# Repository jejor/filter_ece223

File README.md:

# Filter Project for ECE223PSU/MCECS-2019

This repo contains information pertaining to a four branch 6th order passive Butterworth filters, with volume indicators, music box.
This project was completed to meet the 2018-2019 Electrical Engineering 221-223 sequence course requirements taught by Dr. Donald Duncan at Portland State University Maseeh College of Engineering and Computer Science - Electrical Engineering Program. 

View the project final report [here](/docs/finalreport.pdf) or by using the [google doc link](https://docs.google.com/document/d/1vV6OJEWidjzbffv2h6qe4K4YXA2pBC030I1_OhE0v94/edit?usp=sharing)

Note: Github documentation is currently in progress. Refer to the doc/finalreport.pdf until github documentation is completed.

# Filter Project Information

## Project Purpose

The function of this project is to filter an audio signal and indicate, by light, the filtered frequency presence. The audio signal is filtered through four branches, each filter branch has its own adjustable volume/LED indicator which is activated when a signal passes through the filter branch. Below is the block diagram for the circuit design,

## Project Parts

### [Audio/Input Signal](/docs/input_signal.md)

The audio signal (input signal) must fall within human range of hearing (typically 20-20000 Hz). The input into the system is a 3.5mm auxiliary audio connection. The audio is split into a stereo (binaural) and a mono (mixed) branch. The audio system design ensures that the music played over the speakers is kept separate as left and right audio channels and the filtered signal contains all the audio data. The audio data splits are made using NE5532 op amps used as buffers.

Note: The signal input is connected via screw terminal which allows for signal input modularity. Therefore, the 3.5mm auxiliary cable input into the filter branches and following volume indicator circuit can be removed to insert different signal generator.

### [Filter Branches](/docs/filters.md)

There are four 6th order passive Butterworth equal termination filters; one low-pass, two band-passes, and a high pass. These filters are routied and mounted on a custom designed PCB.

Note: 
- Low-Pass: < 200 Hz
- Band-Pass 1: 250 Hz to 4 kHz
- Band-Pass 2: 4.05 kHz to 9.95 kHz
- High-Pass: > 10 kHz

### [Volume Indicators](/docs/volume.md)

At the end of each filter branch is a LED volume indicator circuit. These circuits contain a series of LEDs and an LM3915 (resistor and comparator network). This circuit is used to indicate when an audio signal satisfies the filter frequencies and passes through that branch; the LM3915 is used to indicate the intensity (i.e. volume) of the signal. These circuits will have the display of two rows of 5 green, 3 yellow, and 2 red LEDs, totalling 20 LEDs per branch. There are a total of four volume indicators, each receiving an amplified signal from a filter.  The intensity of each volume indicator is controllable via a potentiometer controlling the gainstage on its respective filter. These circuits were routed and mounted on a custom designed PCB.

### [Power System](/docs/power.md)

Power Requirements:
- Op Amps, +18V and -18V
- LM3915, 12-20V
- LEDs, 3-5V
- Common Ground

To satisfy the power requirements the project uses a total of seven 9V batteries. These seven batteries are split between three battery packs with a common ground. The first battery pack powers all the op amp rails, it is four 9V batteries in series with a voltage divider to define a common ground and supply the +18V and -18V. The second battery pack powers the volume indicator circuit main power and contains two 9V batteries in series to supply +18V. The third battery pack powers the LEDs in the volume indicator circuit by using a single 9V and an LM317 voltage regulator to supply 3.3V.

### [Housing](/housing/README.md)

This project is housed within a pressed wood frame.

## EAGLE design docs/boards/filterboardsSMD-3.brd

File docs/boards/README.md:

# EAGLE Boards

Made using EAGLE 9.3.2

There are two boards and schematic pairs in this folder. 

- lm3915LEDv.1.brd and lm3915LEDv.1.sch were both designed and manufacutured by Jennifer Jordan on May 2nd, 2019.
- filterboardsSMD-3.brd and filterboardsSMD-3.sch were both designed and manufactured by David Lay (dalay@pdx.edu) on May 29th, 2019.

The completed boards can be seen below,

- lm3915LEDv.1 Front

- Back

- filterboardsSMD-3 Front (credit: David Lay)

- Back (credit: David Lay)

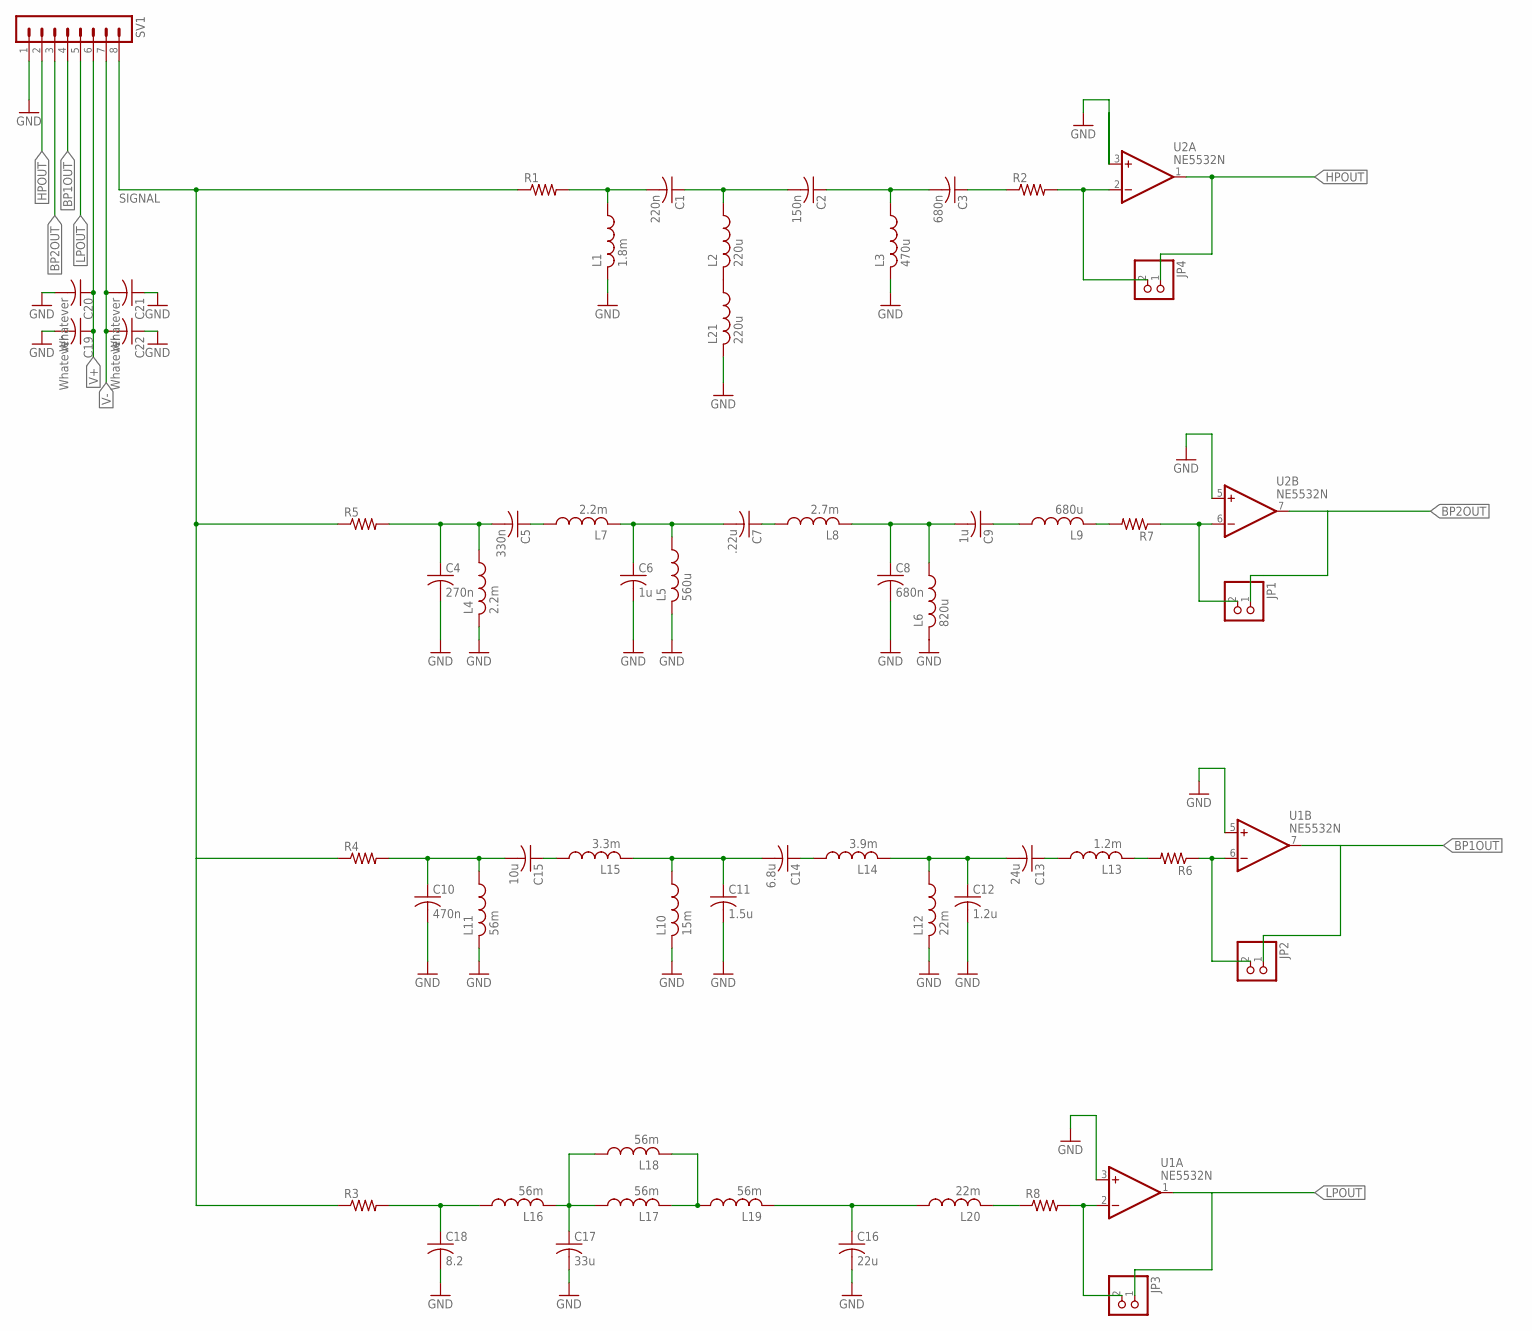
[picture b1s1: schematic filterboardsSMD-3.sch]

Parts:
C1: 220n; C0805K
C2: 150n; C025-030X050
C3, C8: 680n; C025-030X050
C4: 270n; C025-030X050
C5: 330n; C025-030X050
C6, C9: 1u; C1210K
C7: .22u; C0805K
C10: 470n; C025-030X050
C11: 1.5u; C0805K
C12: 1.2u; C102-054X133
C13: 24u; C025-030X050
C14: 6.8u; C025-030X050
C15: 10u; C1206K
C16: 22u; C025-030X050
C17: 33u; C025-030X050
C18: 8.2; C1210K
C19, C20, C21, C22: Whatever; C050-025X075
JP1, JP2, JP3, JP4: PINHD-1X2; 1X02
L1: 1.8m; 0207/5V
L2, L21: 220u; 0207/5V
L3: 470u; 0207/5V
L4, L7: 2.2m; 0207/5V
L5: 560u; 0207/5V
L6: 820u; 0207/5V
L8: 2.7m; 0207/5V
L9: 680u; 0207/5V
L10: 15m; 0207/5V
L11, L16, L17, L18, L19: 56m; 0207/5V
L12, L20: 22m; 0207/5V
L13: 1.2m; 0207/5V
L14: 3.9m; 0207/5V
L15: 3.3m; 0207/5V
R1, R2, R3, R4, R5, R6, R7, R8: R-US_0204/7; 0204/7
SV1: MA08-1
U1, U2: NE5532N; DIL08

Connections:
BP1OUT: JP2.1, SV1.4, U1.7 (OUT)
BP2OUT: JP1.1, SV1.3, U2.7 (OUT)
GND: C4.2, C6.2, C8.2, C10.2, C11.2, C12.2, C16.2, C17.2, C18.2, C19.2, C20.2, C21.1, C22.1, L1.2, L3.2, L4.2, L5.2, L6.2, L10.2, L11.2, L12.2, L21.2, SV1.1, U1.3 (+IN), U1.5 (+IN), U2.5 (+IN)
HPOUT: JP4.1, SV1.2, U2.1 (OUT)
LPOUT: JP3.1, SV1.5, U1.1 (OUT)
unnamed: C1.2, L1.1, R1.2
unnamed: C1.1, C2.2, L2.1
unnamed: C2.1, C3.2, L3.1
unnamed: C3.1, R2.1
unnamed: C4.1, C5.2, L4.1, R5.2
unnamed: C5.1, L7.1
unnamed: C6.1, C7.2, L5.1, L7.2
unnamed: JP3.2, R8.2, U1.2 (-IN)
unnamed: C7.1, L8.1
unnamed: C8.1, C9.2, L6.1, L8.2
unnamed: C9.1, L9.1
unnamed: JP2.2, R6.1, U1.6 (-IN)
unnamed: JP1.2, R7.1, U2.6 (-IN)
unnamed: L9.2, R7.2
unnamed: JP4.2, R2.2, U2.2 (-IN)
unnamed: C10.1, C15.2, L11.1, R4.2
unnamed: C15.1, L15.1
unnamed: C11.1, C14.2, L10.1, L15.2
unnamed: L2.2, L21.1
unnamed: C14.1, L14.1
unnamed: C12.1, C13.2, L12.1, L14.2
unnamed: C13.1, L13.1
unnamed: L13.2, R6.2
unnamed: C18.1, L16.1, R3.2
unnamed: C17.1, L16.2, L17.1, L18.1
unnamed: L17.2, L18.2, L19.1
unnamed: C16.1, L19.2, L20.1
unnamed: L20.2, R8.1
SIGNAL: R1.1, R3.1, R4.1, R5.1, SV1.8
V+: C19.1, C20.1, SV1.6, U1.8 (V+), U2.8 (V+)
V-: C21.2, C22.2, SV1.7, U1.4 (V-), U2.4 (V-)

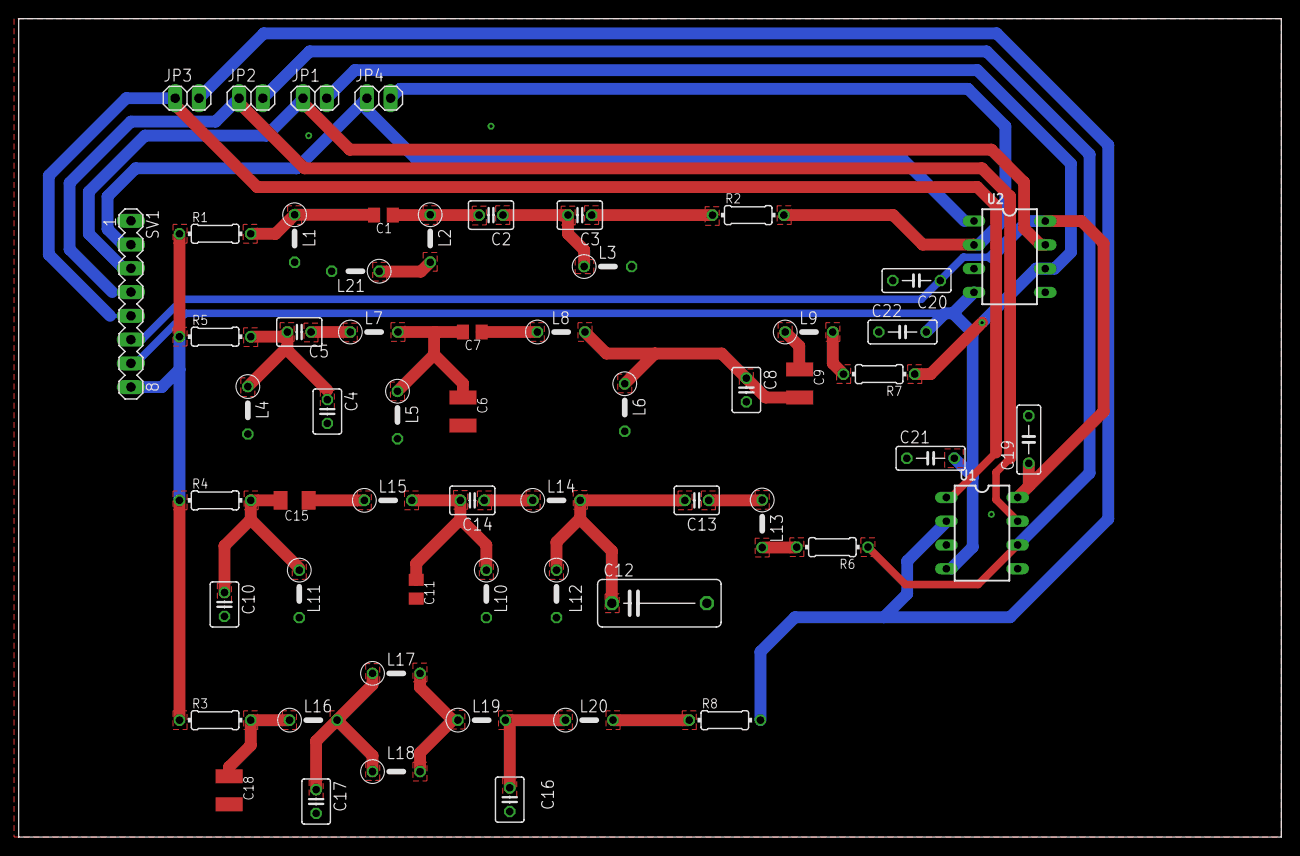
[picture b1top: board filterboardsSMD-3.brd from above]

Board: 2 copper layers, 135.0 x 87.5 mm, 58 parts (0 on the bottom side), 36 nets.

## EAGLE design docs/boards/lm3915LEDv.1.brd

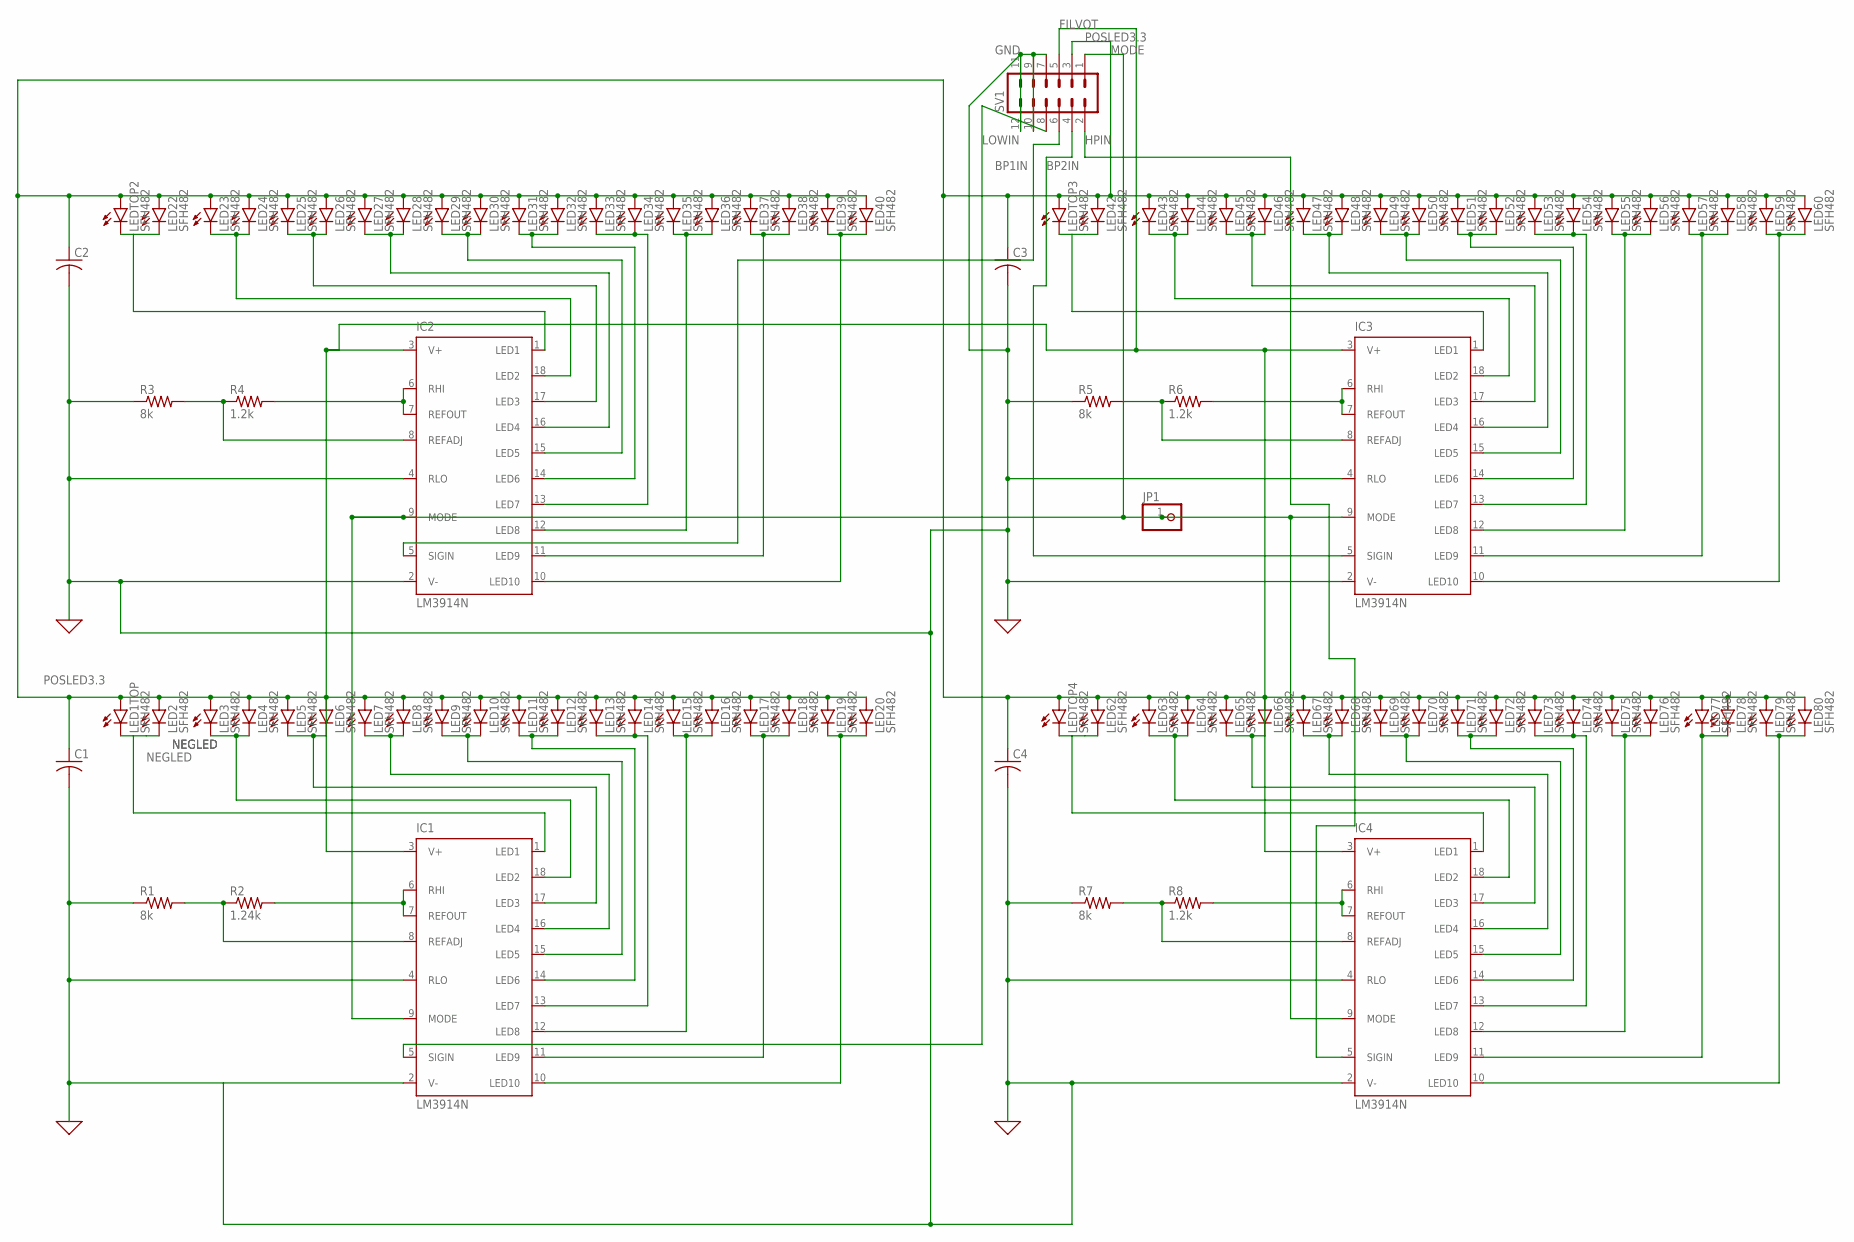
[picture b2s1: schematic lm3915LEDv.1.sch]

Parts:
C1, C2, C3, C4: C-US025-030X050; C025-030X050
IC1, IC2, IC3, IC4: LM3914N; DIL18
JP1: PINHD-1X1; 1X01
LED1TOP, LED2, LED3, LED4, LED5, LED6, LED7, LED8, LED9, LED10, LED11, LED12, LED13, LED14, LED15, LED16, LED17, LED18, LED19, LED20, LED22, LED23, LED24, LED25, LED26, LED27, LED28, LED29, LED30, LED31, LED32, LED33, LED34, LED35, LED36, LED37, LED38, LED39, LED40, LED42, LED43, LED44, LED45, LED46, LED47, LED48, LED49, LED50, LED51, LED52, LED53, LED54, LED55, LED56, LED57, LED58, LED59, LED60, LED62, LED63, LED64, LED65, LED66, LED67, LED68, LED69, LED70, LED71, LED72, LED73, LED74, LED75, LED76, LED77, LED78, LED79, LED80: SFH482
LEDTOP2, LEDTOP3, LEDTOP4: SFH482
R1, R3, R5, R7: 8k; 0207/10
R2: 1.24k; 0207/10
R4, R6, R8: 1.2k; 0207/10
SV1: MA06-2

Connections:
BP1IN: IC2.5 (SIGIN), SV1.6
BP2IN: IC3.5 (SIGIN), SV1.4
FILVOT: IC1.3 (V+), IC2.3 (V+), IC3.3 (V+), IC4.3 (V+), SV1.5
GND: C1.2, C2.2, C3.2, C4.2, IC1.2 (V-), IC1.4 (RLO), IC2.2 (V-), IC2.4 (RLO), IC3.2 (V-), IC3.4 (RLO), IC4.2 (V-), IC4.4 (RLO), R1.1, R3.1, R5.1, R7.1, SV1.7, SV1.9, SV1.10, SV1.11, SV1.12
HPIN: IC4.5 (SIGIN), SV1.2
LOWIN: IC1.5 (SIGIN), SV1.8
MODE: IC1.9 (MODE), IC2.9 (MODE), IC3.9 (MODE), IC4.9 (MODE), JP1.1, SV1.1
unnamed: IC1.18 (LED2), LED3.K (C), LED4.K (C)
unnamed: IC1.17 (LED3), LED5.K (C), LED6.K (C)
unnamed: IC1.16 (LED4), LED7.K (C), LED8.K (C)
unnamed: IC1.15 (LED5), LED9.K (C), LED10.K (C)
unnamed: IC1.14 (LED6), LED11.K (C), LED12.K (C)
unnamed: IC1.13 (LED7), LED13.K (C), LED14.K (C)
unnamed: IC1.12 (LED8), LED15.K (C), LED16.K (C)
unnamed: IC1.11 (LED9), LED17.K (C), LED18.K (C)
unnamed: IC1.10 (LED10), LED19.K (C), LED20.K (C)
unnamed: IC4.1 (LED1), LED62.K (C), LEDTOP4.K (C)
unnamed: IC2.1 (LED1), LED22.K (C), LEDTOP2.K (C)
unnamed: IC2.18 (LED2), LED23.K (C), LED24.K (C)
unnamed: IC2.17 (LED3), LED25.K (C), LED26.K (C)
unnamed: IC2.16 (LED4), LED27.K (C), LED28.K (C)
unnamed: IC2.15 (LED5), LED29.K (C), LED30.K (C)
unnamed: IC1.6 (RHI), IC1.7 (REFOUT), R2.2
unnamed: IC1.8 (REFADJ), R1.2, R2.1
unnamed: IC2.14 (LED6), LED31.K (C), LED32.K (C)
unnamed: IC2.13 (LED7), LED33.K (C), LED34.K (C)
unnamed: IC2.12 (LED8), LED35.K (C), LED36.K (C)
unnamed: IC2.11 (LED9), LED37.K (C), LED38.K (C)
unnamed: IC2.10 (LED10), LED39.K (C), LED40.K (C)
unnamed: IC2.6 (RHI), IC2.7 (REFOUT), R4.2
unnamed: IC2.8 (REFADJ), R3.2, R4.1
unnamed: IC3.1 (LED1), LED42.K (C), LEDTOP3.K (C)
unnamed: IC3.18 (LED2), LED43.K (C), LED44.K (C)
unnamed: IC3.17 (LED3), LED45.K (C), LED46.K (C)
unnamed: IC3.16 (LED4), LED47.K (C), LED48.K (C)
unnamed: IC3.15 (LED5), LED49.K (C), LED50.K (C)
unnamed: IC3.14 (LED6), LED51.K (C), LED52.K (C)
unnamed: IC3.13 (LED7), LED53.K (C), LED54.K (C)
unnamed: IC3.12 (LED8), LED55.K (C), LED56.K (C)
unnamed: IC3.11 (LED9), LED57.K (C), LED58.K (C)
unnamed: IC3.10 (LED10), LED59.K (C), LED60.K (C)
unnamed: IC3.6 (RHI), IC3.7 (REFOUT), R6.2
unnamed: IC3.8 (REFADJ), R5.2, R6.1
unnamed: IC4.18 (LED2), LED63.K (C), LED64.K (C)
unnamed: IC4.17 (LED3), LED65.K (C), LED66.K (C)
unnamed: IC4.16 (LED4), LED67.K (C), LED68.K (C)
unnamed: IC4.15 (LED5), LED69.K (C), LED70.K (C)
unnamed: IC4.14 (LED6), LED71.K (C), LED72.K (C)
unnamed: IC4.13 (LED7), LED73.K (C), LED74.K (C)
unnamed: IC4.12 (LED8), LED75.K (C), LED76.K (C)
unnamed: IC4.11 (LED9), LED77.K (C), LED78.K (C)
unnamed: IC4.10 (LED10), LED79.K (C), LED80.K (C)
unnamed: IC4.6 (RHI), IC4.7 (REFOUT), R8.2
unnamed: IC4.8 (REFADJ), R7.2, R8.1
NEGLED: IC1.1 (LED1), LED1TOP.K (C), LED2.K (C)
POSLED3.3: C1.1, C2.1, C3.1, C4.1, LED1TOP.A, LED2.A, LED3.A, LED4.A, LED5.A, LED6.A, LED7.A, LED8.A, LED9.A, LED10.A, LED11.A, LED12.A, LED13.A, LED14.A, LED15.A, LED16.A, LED17.A, LED18.A, LED19.A, LED20.A, LED22.A, LED23.A, LED24.A, LED25.A, LED26.A, LED27.A, LED28.A, LED29.A, LED30.A, LED31.A, LED32.A, LED33.A, LED34.A, LED35.A, LED36.A, LED37.A, LED38.A, LED39.A, LED40.A, LED42.A, LED43.A, LED44.A, LED45.A, LED46.A, LED47.A, LED48.A, LED49.A, LED50.A, LED51.A, LED52.A, LED53.A, LED54.A, LED55.A, LED56.A, LED57.A, LED58.A, LED59.A, LED60.A, LED62.A, LED63.A, LED64.A, LED65.A, LED66.A, LED67.A, LED68.A, LED69.A, LED70.A, LED71.A, LED72.A, LED73.A, LED74.A, LED75.A, LED76.A, LED77.A, LED78.A, LED79.A, LED80.A, LEDTOP2.A, LEDTOP3.A, LEDTOP4.A, SV1.3

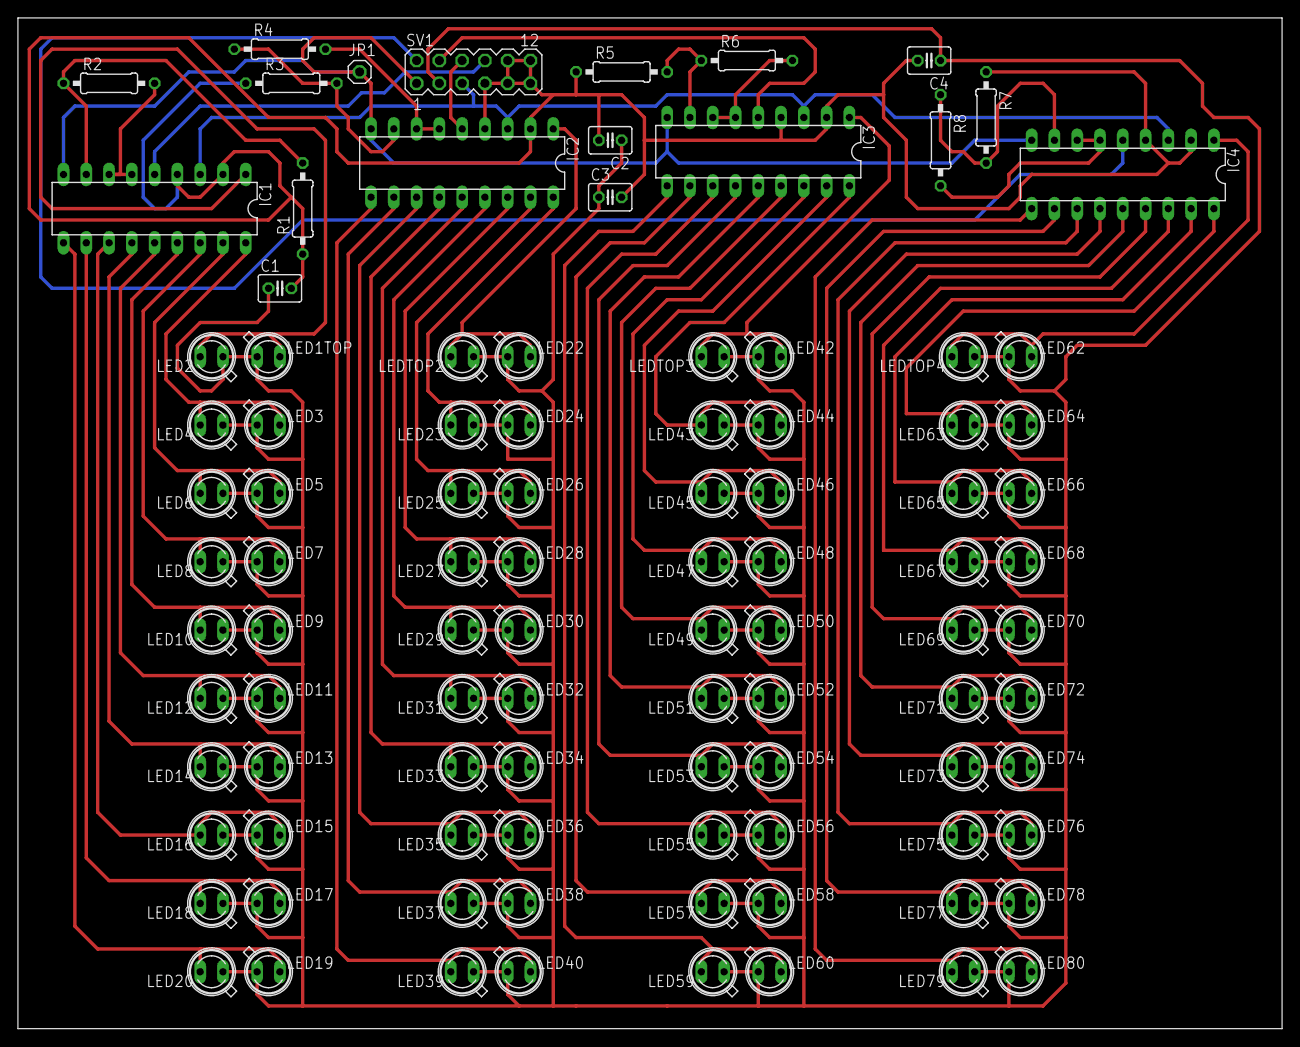
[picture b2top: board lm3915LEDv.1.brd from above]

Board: 2 copper layers, 140.9 x 112.7 mm, 98 parts (0 on the bottom side), 56 nets.

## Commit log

2019-07-16 Create report
2019-07-16 updated final report link to temp google doc
2019-07-16 spelling
2019-07-16 upload final report
2019-07-16 Create LPcomponentCalcs
2019-07-16 Create LPtf
2019-07-17 upload low pass matlab code
2019-07-17 uploaded low pass linear analysis results
2019-07-17 Create BP1componentCalcs
2019-07-17 band pass 1 matlab code upload
2019-07-17 upload band pass 1 linear analysis results
2019-07-17 Create BP2componentCalcs
2019-07-17 transfer function calcs bp2
2019-07-17 matlab code for band pass 2
2019-07-17 linear analysis band pass 2 results upload
2019-07-17 Create HPcomponentCalcs
2019-07-17 Create HPtf
2019-07-17 matlab high pass filter
2019-07-17 high pass linear analysis results upload
2019-07-17 corrected links
2019-07-17 test
2019-07-17 Rename LPtf to LPtf.md
2019-07-17 update to links
2019-07-17 insert basic transfer function info
2019-07-17 insert basic component calc info
2019-07-17 insert basic transfer function bp2
2019-07-17 insert basic component calc info hp
2019-07-17 insert basic transfer function hp info
2019-07-17 Create Low_PassLT
2019-07-17 updated link
2019-07-17 link correction
2019-07-17 readme image upload
2019-07-17 added links

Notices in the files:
parts and their libraries:
op-amp: Copyright (C) 2006 by Bob Starr
